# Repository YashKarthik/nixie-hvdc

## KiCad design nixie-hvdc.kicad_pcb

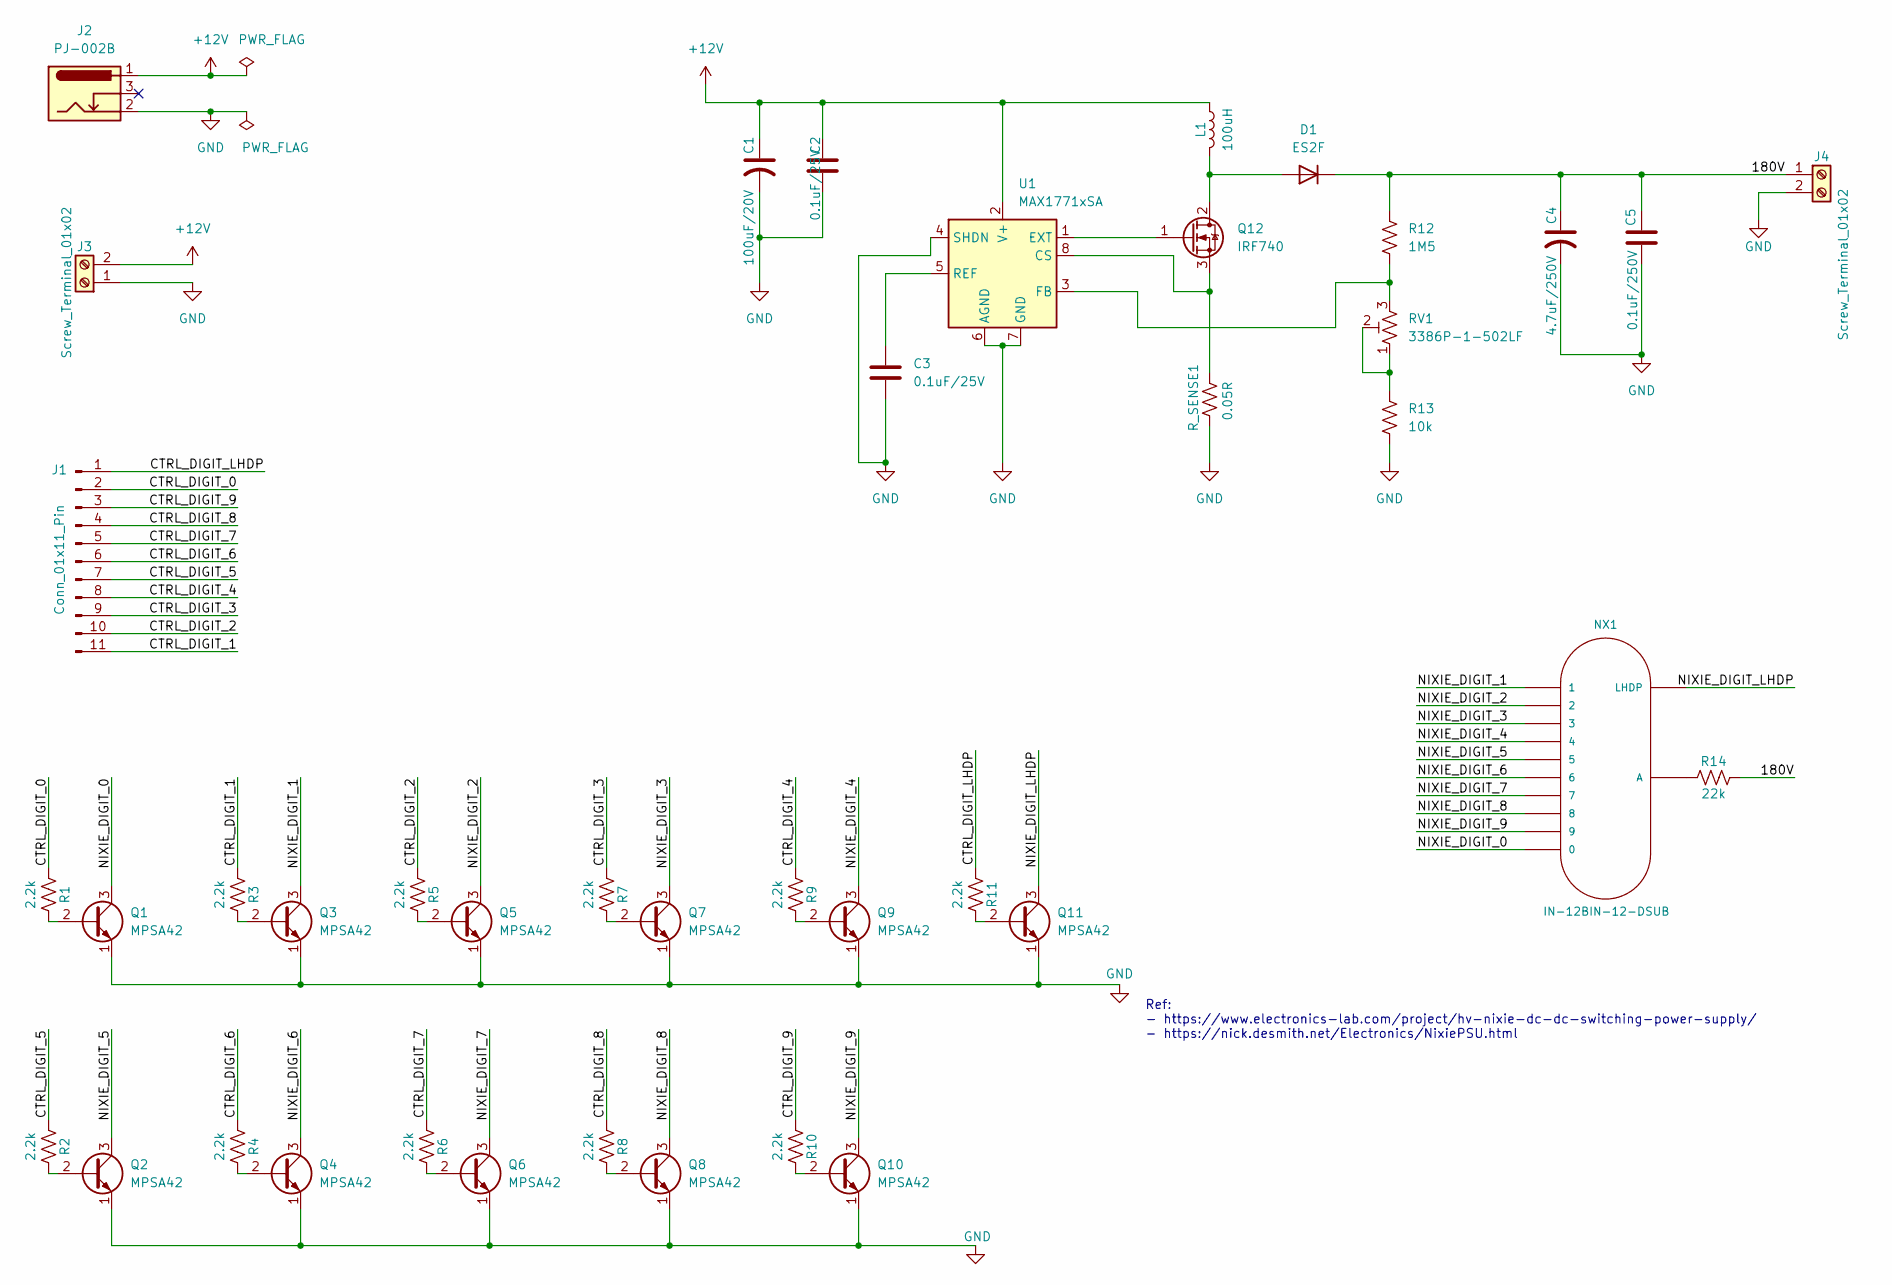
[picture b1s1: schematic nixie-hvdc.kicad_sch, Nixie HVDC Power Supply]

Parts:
C1: 100uF/20V; CP_EIA-7343-31_Kemet-D_HandSolder; LCSC Part No. C122302
C2, C3: 0.1uF/25V; C_0805_2012Metric_Pad1.18x1.45mm_HandSolder; LCSC Part No. C396718
C4: 4.7uF/250V; CP_Elec_8x10.5; DigiKey Part No. 493-9983-2-ND
C5: 0.1uF/250V; C_1210_3225Metric_Pad1.33x2.70mm_HandSolder; LCSC Part No. C52020
D1: ES2F; D_SMB-SMC_Universal_Handsoldering; MFR Part No. ES2GB; LCSC Part No. C2844160
J1: Conn_01x11_Pin; PinHeader_1x11_P2.54mm_Vertical
J2: PJ-002B; CUI_PJ-002B; MFR Part No. PJ-002B; LCSC Part No. C22359705
J3, J4: Screw_Terminal_01x02; TerminalBlock_Phoenix_MKDS-1,5-2-5.08_1x02_P5.08mm_Horizont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; MFR Part No. MKDS 1,5/ 2-5,08; LCSC Part No. C5183929
L1: 100uH; L_12x12mm_H6mm; LCSC Part No. C2962892
NX1: IN-12BIN-12-DSUB; nixies-us-IN-12-DSUB
Q1, Q2, Q3, Q4, Q5, Q6, Q7, Q8, Q9, Q10, Q11: MPSA42; TO-92; MFR Part No. MPSA42; LCSC Part No. C305411
Q12: IRF740; TO-220-3_Vertical; MFR Part No. IRF740PBF; LCSC Part No. C34373758
R1, R2, R3, R4, R5, R6, R7, R8, R9, R10, R11: 2.2k; R_0805_2012Metric_Pad1.20x1.40mm_HandSolder; LCSC Part No. C269724
R12: 1M5; R_0805_2012Metric_Pad1.20x1.40mm_HandSolder; LCSC Part No. 125mW Thick Film Resistor ±200ppm/℃ ±1%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
R13: 10k; R_0805_2012Metric_Pad1.20x1.40mm_HandSolder; LCSC Part No. C269724
R14: 22k; R_0805_2012Metric_Pad1.20x1.40mm_HandSolder; LCSC Part No. C269724
RV1: 3386P-1-502LF; Potentiometer_Bourns_3386P_Vertical; MFR Part No. 3386P-1-502LF; LCSC Part No. C22461636
R_SENSE1: 0.05R; R_1206_3216Metric_Pad1.30x1.75mm_HandSolder; LCSC Part No. C149662
U1: MAX1771xSA; SO-8_3.9x4.9mm_P1.27mm; MFR Part No. MAX1771; LCSC Part No. C407903

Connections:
+12V: C1.1, C2.1, J2.1, J3.2, L1.1, U1.2 (V+)
/180V: C4.1, C5.1, D1.1 (K), J4.1, R12.1, R14.2
/CTRL_DIGIT_0: J1.2, R1.1
/CTRL_DIGIT_1: J1.11, R3.1
/CTRL_DIGIT_2: J1.10, R5.1
/CTRL_DIGIT_3: J1.9, R7.1
/CTRL_DIGIT_4: J1.8, R9.1
/CTRL_DIGIT_5: J1.7, R2.1
/CTRL_DIGIT_6: J1.6, R4.1
/CTRL_DIGIT_7: J1.5, R6.1
/CTRL_DIGIT_8: J1.4, R8.1
/CTRL_DIGIT_9: J1.3, R10.1
/CTRL_DIGIT_LHDP: J1.1, R11.1
/NIXIE_DIGIT_0: NX1.0, Q1.3 (C)
/NIXIE_DIGIT_1: NX1.1, Q3.3 (C)
/NIXIE_DIGIT_2: NX1.2, Q5.3 (C)
/NIXIE_DIGIT_3: NX1.3, Q7.3 (C)
/NIXIE_DIGIT_4: NX1.4, Q9.3 (C)
/NIXIE_DIGIT_5: NX1.5, Q2.3 (C)
/NIXIE_DIGIT_6: NX1.6, Q4.3 (C)
/NIXIE_DIGIT_7: NX1.7, Q6.3 (C)
/NIXIE_DIGIT_8: NX1.8, Q8.3 (C)
/NIXIE_DIGIT_9: NX1.9, Q10.3 (C)
/NIXIE_DIGIT_LHDP: NX1.LHDP, Q11.3 (C)
GND: C1.2, C2.2, C3.2, C4.2, C5.2, J2.2, J3.1, J4.2, Q1.1 (E), Q2.1 (E), Q3.1 (E), Q4.1 (E), Q5.1 (E), Q6.1 (E), Q7.1 (E), Q8.1 (E), Q9.1 (E), Q10.1 (E), Q11.1 (E), R13.2, R_SENSE1.2, U1.4 (SHDN), U1.6 (AGND), U1.7 (GND)
unnamed: D1.2 (A), L1.2, Q12.2 (D)
unnamed: NX1.A, R14.1
unnamed: Q1.2 (B), R1.2
unnamed: Q2.2 (B), R2.2
unnamed: Q3.2 (B), R3.2
unnamed: Q4.2 (B), R4.2
unnamed: Q5.2 (B), R5.2
unnamed: Q6.2 (B), R6.2
unnamed: Q7.2 (B), R7.2
unnamed: Q8.2 (B), R8.2
unnamed: Q9.2 (B), R9.2
unnamed: Q10.2 (B), R10.2
unnamed: Q11.2 (B), R11.2
unnamed: Q12.1 (G), U1.1 (EXT)
unnamed: Q12.3 (S), R_SENSE1.1, U1.8 (CS)
unnamed: R13.1, RV1.1, RV1.2
unnamed: R12.2, RV1.3, U1.3 (FB)
unnamed: C3.1, U1.5 (REF)

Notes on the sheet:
Ref: - https://www.electronics-lab.com/project/hv-nixie-dc-dc-switching-power-supply/ - https://nick.desmith.net/Electronics/NixiePSU.html

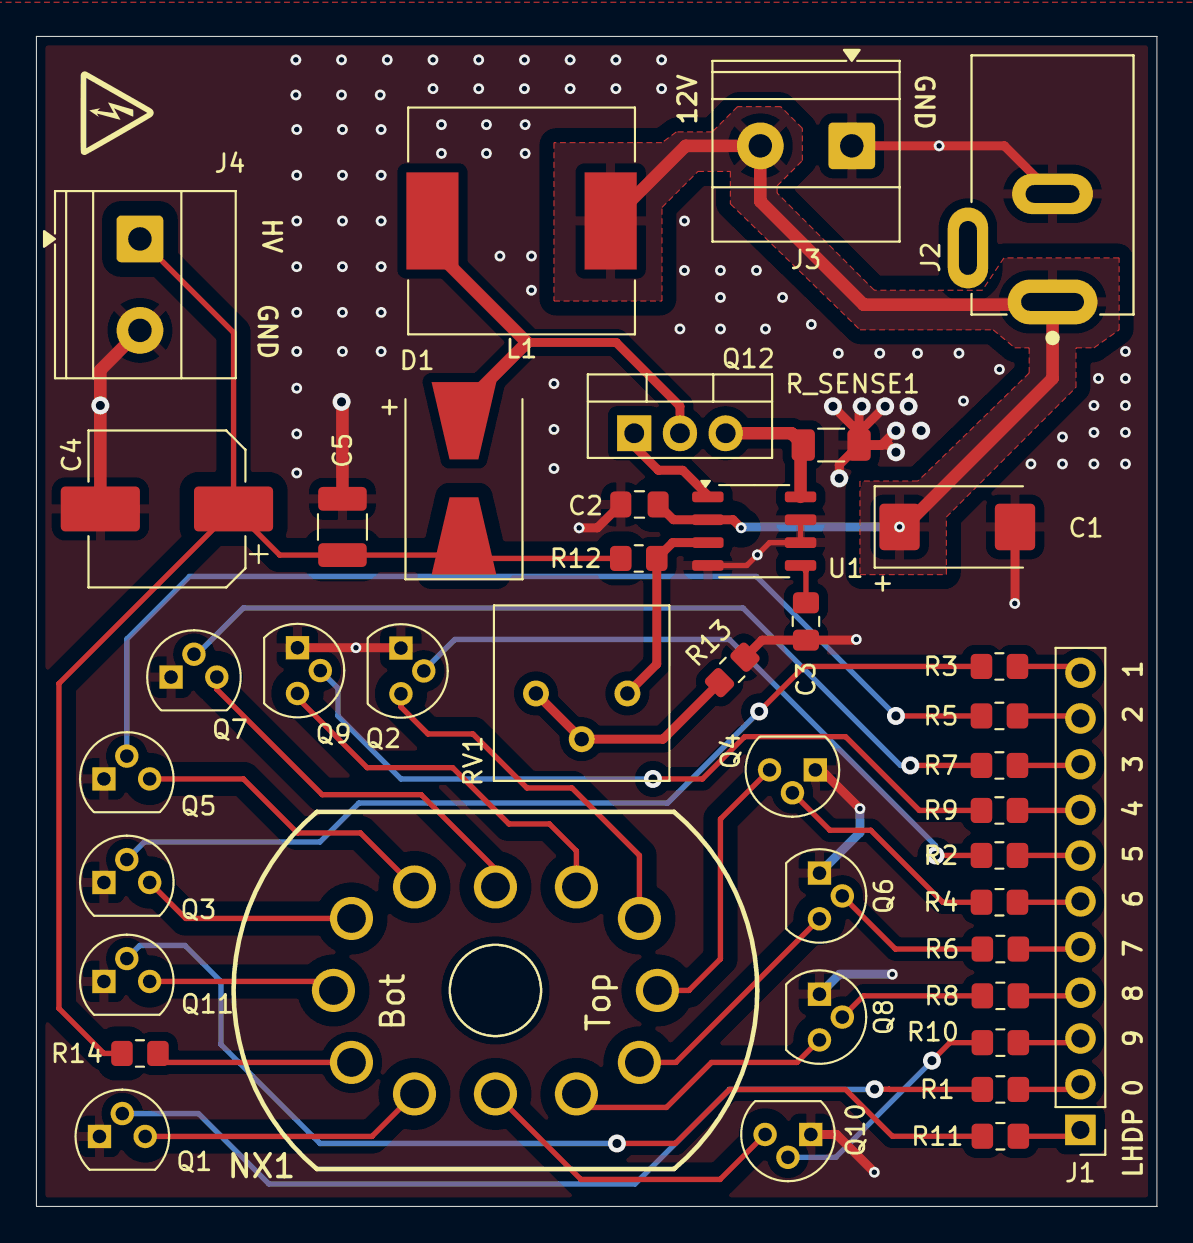
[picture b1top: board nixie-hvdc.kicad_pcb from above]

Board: 2 copper layers, 62.2 x 65.0 mm, 41 parts (0 on the bottom side), 43 nets.

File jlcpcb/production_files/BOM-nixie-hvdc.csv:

Comment,Designator,Footprint,LCSC,Quantity
100uF/20V,C1,CP_EIA-7343-31_Kemet-D_HandSolder,C122302,1
0.05R,R_SENSE1,R_1206_3216Metric_Pad1.30x1.75mm_HandSolder,C149662,1
PJ-002B,J2,CUI_PJ-002B,C22359705,1
3386P-1-502LF,RV1,Potentiometer_Bourns_3386P_Vertical,C22461636,1
2.2k,"R1,R10,R11,R13,R14,R2,R3,R4,R5,R6,R7,R8,R9",R_0805_2012Metric_Pad1.20x1.40mm_HandSolder,C269724,13
ES2F,D1,D_SMB-SMC_Universal_Handsoldering,C2844160,1
100uH,L1,L_12x12mm_H6mm,C2962892,1
MPSA42,"Q1,Q10,Q11,Q2,Q3,Q4,Q5,Q6,Q7,Q8,Q9",TO-92,C305411,11
IRF740,Q12,TO-220-3_Vertical,C34373758,1
0.1uF/25V,"C2,C3",C_0805_2012Metric_Pad1.18x1.45mm_HandSolder,C396718,2
MAX1771xSA,U1,SO-8_3.9x4.9mm_P1.27mm,C407903,1
Screw_Terminal_01x02,"J3,J4","TerminalBlock_Phoenix_MKDS-1,5-2-5.08_1x02_P5.08mm_Horizontal",C5183929,2
0.1uF/250V,C5,C_1210_3225Metric_Pad1.33x2.70mm_HandSolder,C52020,1
IN-12BIN-12-DSUB,NX1,nixies-us-IN-12-DSUB,,1
4.7uF/250V,C4,CP_Elec_8x10.5,,1
1M5,R12,R_0805_2012Metric_Pad1.20x1.40mm_HandSolder,,1
Conn_01x11_Pin,J1,PinHeader_1x11_P2.54mm_Vertical,,1

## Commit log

2025-06-24 initial schematic
2025-06-24 almost done
2025-06-25 schematic done, bom done
2025-06-26 starting pcb layout
2025-06-26 more
2025-06-28 nearly done?
2025-06-28 done i think
2025-06-28 more stuff
2025-07-03 change pot
2025-07-03 fet orienatiton, r_sense vias
2025-07-04 fabbing!
